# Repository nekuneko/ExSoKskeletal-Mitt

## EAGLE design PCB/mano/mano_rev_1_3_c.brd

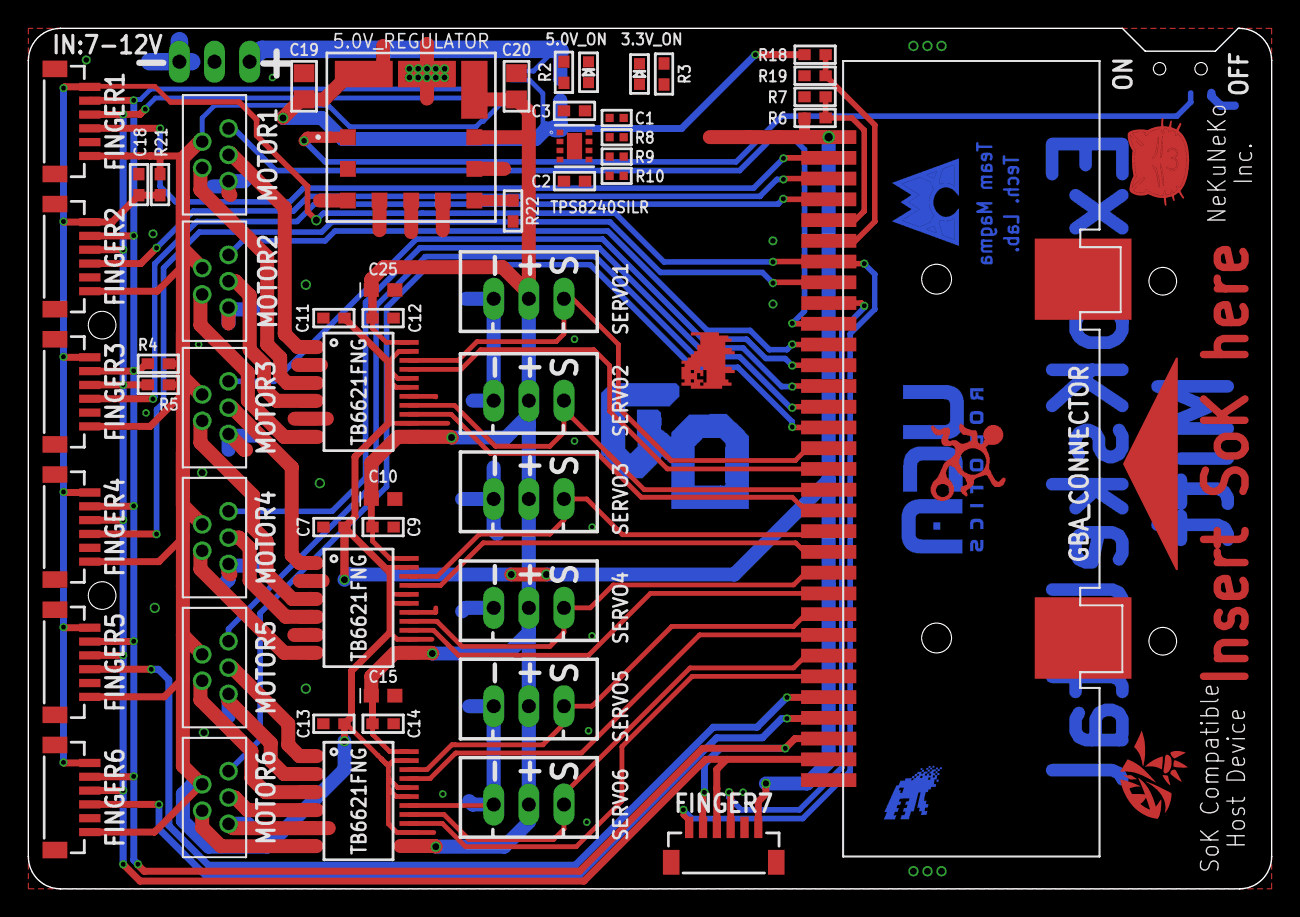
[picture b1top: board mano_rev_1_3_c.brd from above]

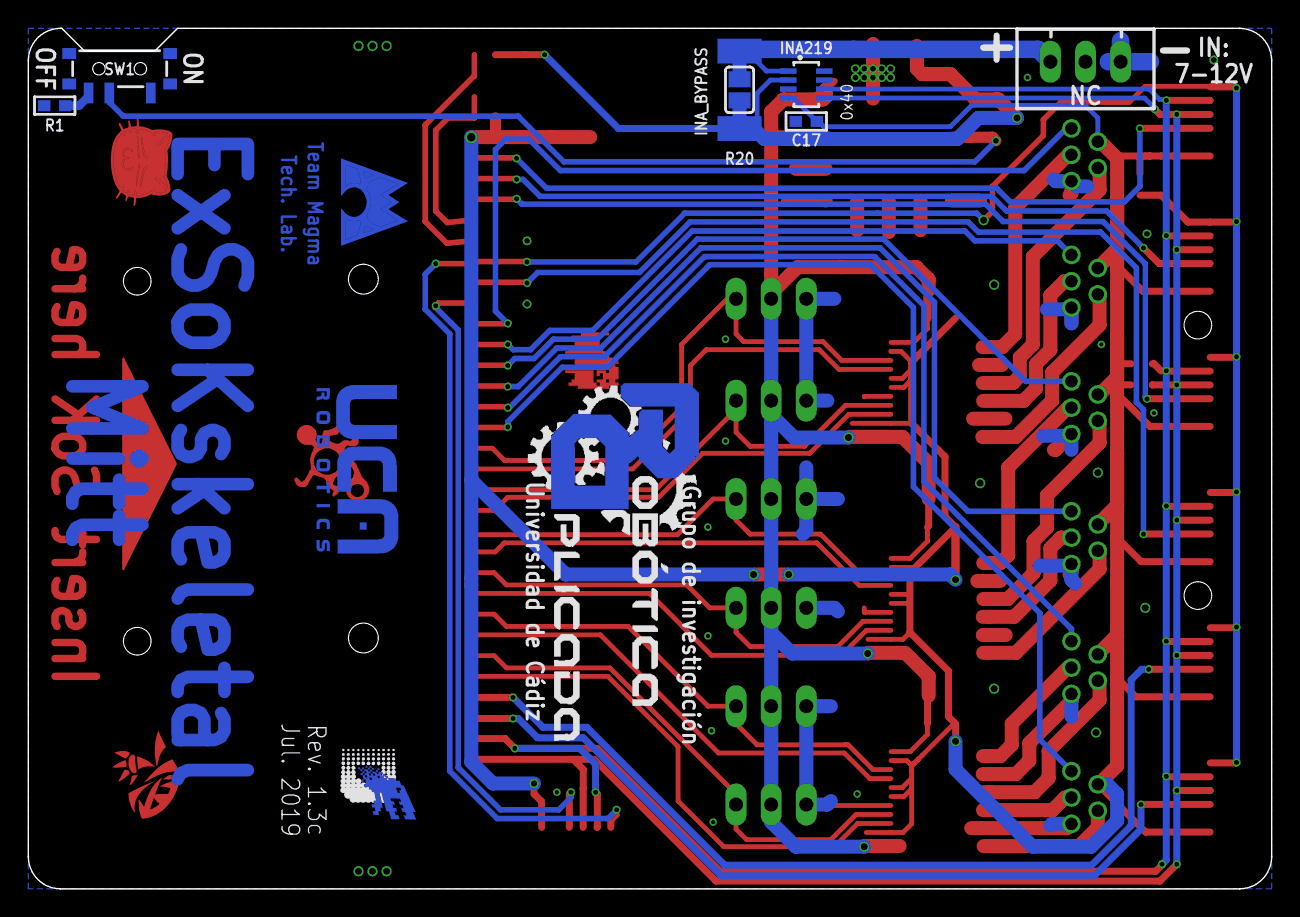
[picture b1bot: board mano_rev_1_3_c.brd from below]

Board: 2 copper layers, 89.9 x 62.2 mm, 71 parts (11 on the bottom side), 55 nets.

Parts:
3.3V_ON, 5.0V_ON: RED; CHIPLED_0603
5.0V_REGULATOR: OKL-T_6-W12P-C; OKL-T3-W12
BATTERY: JST-XH-03-PIN-LONG-PAD; JST-XH-03-PACKAGE-LONG-PAD
C1: 430pF 1mOhm; _0402
C2: 22uF GRM32; _0603
C3: 10uF; _0603
C7, C9, C11, C12, C13, C14, C17: 0.1uF; _0603
C10, C15, C25: 10uF; 0603-POLAR
C18: 1uF; MICROBUILDER__0603
C19: 22uF GRM32; 0805
C20: 47uF GRM32; 0805
FINGER1, FINGER2, FINGER3, FINGER4, FINGER5, FINGER6, FINGER7: BM06B-SRSS-TB(LF)(SN); BM06BSRSSTBLFSN
GBA_CONNECTOR: GBA_CARTRIDGE2
INA219: INA219BIDCNT; SOT23-8
INA_BYPASS: SOLDERJUMPER_REFLOW_NOPASTE
MOTOR1, MOTOR2, MOTOR3, MOTOR4, MOTOR5, MOTOR6: Actuonix PQ12-100-06-P; 5PIN
R1, R2, R3, R6, R21: 10k; _0603
R4, R5: 2.2k; _0603
R7, R19: 33k; _0603
R8, R10: 100k; _0402
R9: 324k; _0402
R18: 51k; _0603
R20: 0.1/1% (PT2512FK-070R1L); 2512
R22: E192 1.33k - 1.35k 0.5% ±100 ppm/ºC; _0603
SERVO1, SERVO2, SERVO3, SERVO4, SERVO5, SERVO6: JST-XH-03-PIN-LONG-PAD; JST-XH-03-PACKAGE-LONG-PAD
SW1: SPDT_SMT_SSSS811101
TB6621FNG: TB6621FNG; SSOP24
TPS8240SILR: TPS82140SILR; SIL0008D
U1, U3: TB6621FNG; SSOP24
U$6: NEKO_6_5_BORDE_TSTOP
U$7: SOK_FINISH
U$8: DOG_FINISH
U$9: MAGMA
U$14: UCAROBOTICS
U$48: GIRA_2_DRAWN_14
U$50: TRIANGLE
U$51: DIGIMON
U$52: BUGS_6

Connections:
3.3V: C2.1, C7.1, C11.1, C13.1, C17.2, FINGER1.1, FINGER2.1, FINGER3.1, FINGER4.1, FINGER5.1, FINGER6.1, FINGER7.1, GBA_CONNECTOR.P$1, INA219.4, MOTOR1.4, MOTOR2.4, MOTOR3.4, MOTOR4.4, MOTOR5.4, MOTOR6.4, R3.1, R4.1, R5.1, R6.1, R8.1, R9.1, R21.1, TB6621FNG.15, TB6621FNG.19, TB6621FNG.20, TB6621FNG.23, TPS8240SILR.4, TPS8240SILR.5, U1.15, U1.19, U1.20, U1.23, U3.15, U3.19, U3.20, U3.23
5.0V: 5.0V_REGULATOR.4, 5.0V_REGULATOR.5, C3.1, C9.2, C10.+, C12.2, C14.2, C15.+, C20.1, C25.+, R2.2, SERVO1.2, SERVO2.2, SERVO3.2, SERVO4.2, SERVO5.2, SERVO6.2, TB6621FNG.13, TB6621FNG.14, TB6621FNG.24, TPS8240SILR.1, TPS8240SILR.2, U1.13, U1.14, U1.24, U3.13, U3.14, U3.24
BATTERY_MONITOR: GBA_CONNECTOR.P$6, R18.1, R19.2
FINGER_!RESET: C18.2, FINGER1.6, FINGER2.6, FINGER3.6, FINGER4.6, FINGER5.6, FINGER6.6, FINGER7.6, GBA_CONNECTOR.P$7, R21.2
FINGER_INT1: FINGER1.3, GBA_CONNECTOR.P$2
FINGER_INT2: FINGER2.3, GBA_CONNECTOR.P$3
FINGER_INT3: FINGER3.3, GBA_CONNECTOR.P$4
FINGER_INT4: FINGER4.3, GBA_CONNECTOR.P$8
FINGER_INT5: FINGER5.3, GBA_CONNECTOR.P$28
FINGER_INT6: FINGER6.3, GBA_CONNECTOR.P$29
FINGER_INT7: FINGER7.3, GBA_CONNECTOR.P$9
GND: 3.3V_ON.C, 5.0V_ON.C, 5.0V_REGULATOR.3, 5.0V_REGULATOR.7, BATTERY.1, C1.2, C2.2, C3.2, C7.2, C9.1, C10.-, C11.2, C12.1, C13.2, C14.1, C15.-, C17.1, C18.1, C19.2, C20.2, C25.-, FINGER1.2, FINGER1.MP1, FINGER1.MP2, FINGER2.2, FINGER2.MP1, FINGER2.MP2, FINGER3.2, FINGER3.MP1, FINGER3.MP2, FINGER4.2, FINGER4.MP1, FINGER4.MP2, FINGER5.2, FINGER5.MP1, FINGER5.MP2, FINGER6.2, FINGER6.MP1, FINGER6.MP2, FINGER7.2, FINGER7.MP1, FINGER7.MP2, GBA_CONNECTOR.P$32, GBA_CONNECTOR.P$33, GBA_CONNECTOR.P$34, INA219.3, INA219.7, INA219.8, MOTOR1.1, MOTOR2.1, MOTOR3.1, MOTOR4.1, MOTOR5.1, MOTOR6.1, R1.1, R7.2, R10.2, R19.1, R22.2, SERVO1.1, SERVO2.1, SERVO3.1, SERVO4.1, SERVO5.1, SERVO6.1, TB6621FNG.3, TB6621FNG.4, TB6621FNG.9, TB6621FNG.10, TB6621FNG.18, TPS8240SILR.3, TPS8240SILR.9, U1.3, U1.4, U1.9, U1.10, U1.18, U3.3, U3.4, U3.9, U3.10, U3.18
MT1A: MOTOR1.2, U1.5, U1.6
MT1B: MOTOR1.3, U1.1, U1.2
MT1_POT: GBA_CONNECTOR.P$10, MOTOR1.5
MT2A: MOTOR2.2, U1.11, U1.12
MT2B: MOTOR2.3, U1.7, U1.8
MT2_POT: GBA_CONNECTOR.P$11, MOTOR2.5
MT3A: MOTOR3.2, U3.5, U3.6
MT3B: MOTOR3.3, U3.1, U3.2
MT3_POT: GBA_CONNECTOR.P$12, MOTOR3.5
MT4A: MOTOR4.2, U3.11, U3.12
MT4B: MOTOR4.3, U3.7, U3.8
MT4_POT: GBA_CONNECTOR.P$13, MOTOR4.5
MT5A: MOTOR5.2, TB6621FNG.5, TB6621FNG.6
MT5B: MOTOR5.3, TB6621FNG.1, TB6621FNG.2
MT5_POT: GBA_CONNECTOR.P$14, MOTOR5.5
MT6A: MOTOR6.2, TB6621FNG.11, TB6621FNG.12
MT6B: MOTOR6.3, TB6621FNG.7, TB6621FNG.8
MT6_POT: GBA_CONNECTOR.P$15, MOTOR6.5
unnamed: R1.2, SW1.C
unnamed: R8.2, TPS8240SILR.7
unnamed: 5.0V_REGULATOR.6, R22.1
unnamed: R9.2, R10.1, TPS8240SILR.6
unnamed: 5.0V_ON.A, R2.1
unnamed: 3.3V_ON.A, R3.2
PWM_MT1A: GBA_CONNECTOR.P$17, U1.21
PWM_MT1B_SERVO1: GBA_CONNECTOR.P$16, SERVO1.3, U1.22
PWM_MT2A_SERVO2: GBA_CONNECTOR.P$18, SERVO2.3, U1.17
PWM_MT2B: GBA_CONNECTOR.P$19, U1.16
PWM_MT3A: GBA_CONNECTOR.P$21, U3.21
PWM_MT3B_SERVO3: GBA_CONNECTOR.P$20, SERVO3.3, U3.22
PWM_MT4A_SERVO4: GBA_CONNECTOR.P$22, SERVO4.3, U3.17
PWM_MT4B: GBA_CONNECTOR.P$23, U3.16
PWM_MT5A: GBA_CONNECTOR.P$25, TB6621FNG.21
PWM_MT5B_SERVO5: GBA_CONNECTOR.P$24, SERVO5.3, TB6621FNG.22
PWM_MT6A_SERVO6: GBA_CONNECTOR.P$26, SERVO6.3, TB6621FNG.17
PWM_MT6B: GBA_CONNECTOR.P$27, TB6621FNG.16
REG_5V_ON: 5.0V_REGULATOR.1, SW1.B
SCL: FINGER1.4, FINGER2.4, FINGER3.4, FINGER4.4, FINGER5.4, FINGER6.4, FINGER7.4, GBA_CONNECTOR.P$31, INA219.5, R5.2
SDA: FINGER1.5, FINGER2.5, FINGER3.5, FINGER4.5, FINGER5.5, FINGER6.5, FINGER7.5, GBA_CONNECTOR.P$30, INA219.6, R4.2
SOK: GBA_CONNECTOR.P$5, R6.2, R7.1
SS_TR: C1.1, TPS8240SILR.8
VBAT: 5.0V_REGULATOR.2, C19.1, INA219.2, INA_BYPASS.1, R18.2, R20.1
VLIPO: BATTERY.3, INA219.1, INA_BYPASS.2, R20.2

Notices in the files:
parts and their libraries:
microbuilder: This work is placed in the public domain, and may be freely used for commercial and non-commercial work with the following conditions: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
SparkFun-Capacitors: Licensing: Creative Commons ShareAlike 4.0 International - https://creativecommons.org/licenses/by-sa/4.0
